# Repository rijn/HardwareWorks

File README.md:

# HardwareWorks
Some hardware module, including schematic, layout and demo code.

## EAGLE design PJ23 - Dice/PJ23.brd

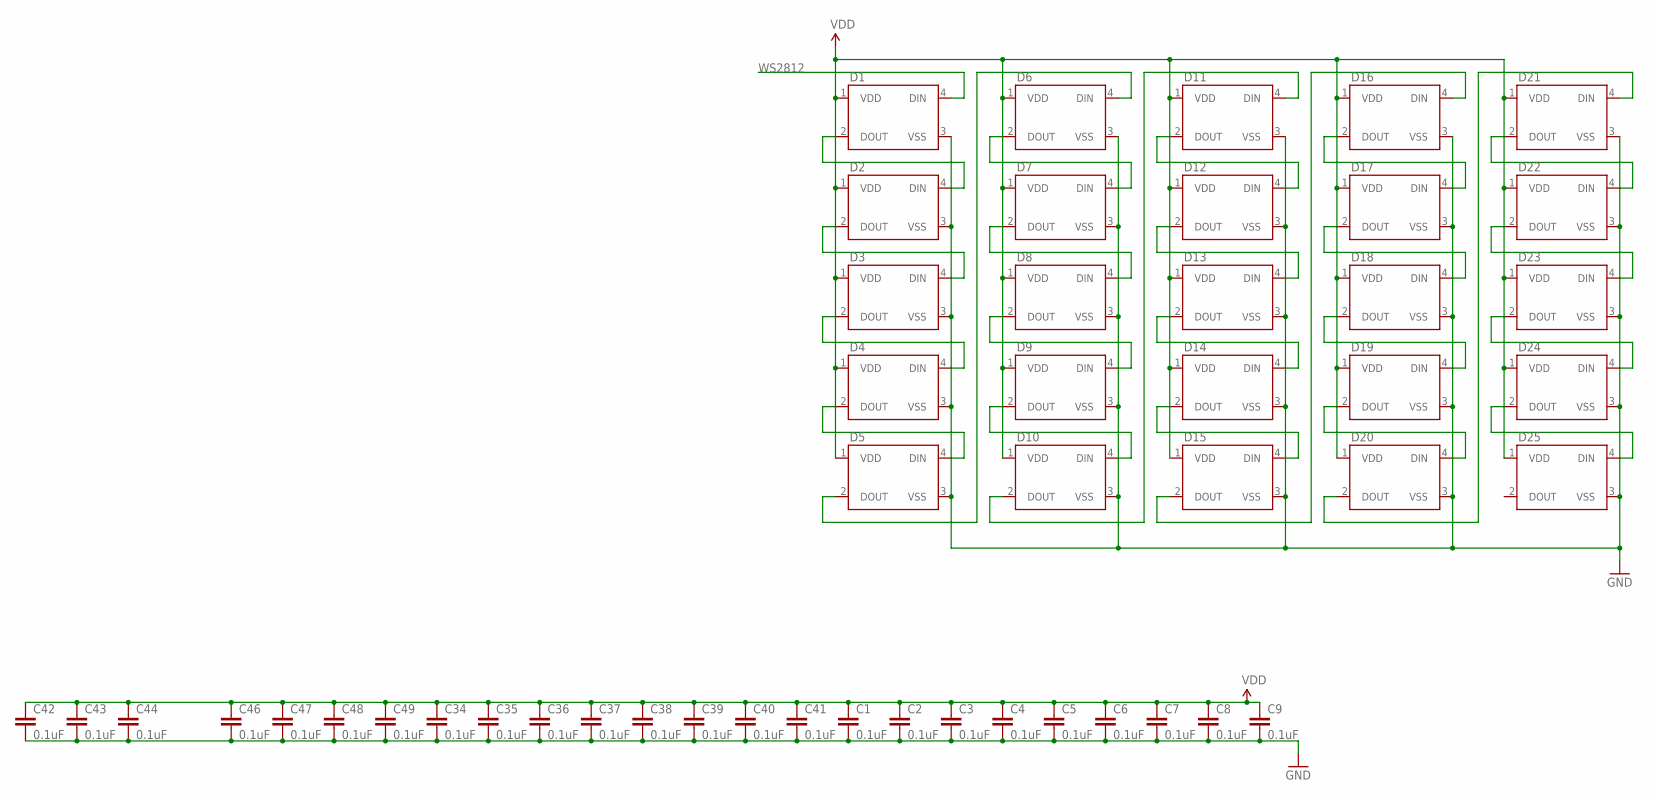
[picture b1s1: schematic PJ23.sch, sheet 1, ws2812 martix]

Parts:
C1, C2, C3, C4, C5, C6, C7, C8, C9, C34, C35, C36, C37, C38, C39, C40, C41, C42, C43, C44, C46, C47, C48, C49: 0.1uF; 0603-CAP
D1, D2, D3, D4, D5, D6, D7, D8, D9, D10, D11, D12, D13, D14, D15, D16, D17, D18, D19, D20, D21, D22, D23, D24, D25: WS2812B

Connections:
GND: C1.2, C2.2, C3.2, C4.2, C5.2, C6.2, C7.2, C8.2, C9.2, C34.2, C35.2, C36.2, C37.2, C38.2, C39.2, C40.2, C41.2, C42.2, C43.2, C44.2, C46.2, C47.2, C48.2, C49.2, D1.3 (VSS), D2.3 (VSS), D3.3 (VSS), D4.3 (VSS), D5.3 (VSS), D6.3 (VSS), D7.3 (VSS), D8.3 (VSS), D9.3 (VSS), D10.3 (VSS), D11.3 (VSS), D12.3 (VSS), D13.3 (VSS), D14.3 (VSS), D15.3 (VSS), D16.3 (VSS), D17.3 (VSS), D18.3 (VSS), D19.3 (VSS), D20.3 (VSS), D21.3 (VSS), D22.3 (VSS), D23.3 (VSS), D24.3 (VSS), D25.3 (VSS); also elsewhere on the board
unnamed: D1.2 (DOUT), D2.4 (DIN)
unnamed: D2.2 (DOUT), D3.4 (DIN)
unnamed: D3.2 (DOUT), D4.4 (DIN)
unnamed: D4.2 (DOUT), D5.4 (DIN)
unnamed: D5.2 (DOUT), D6.4 (DIN)
unnamed: D6.2 (DOUT), D7.4 (DIN)
unnamed: D7.2 (DOUT), D8.4 (DIN)
unnamed: D8.2 (DOUT), D9.4 (DIN)
unnamed: D9.2 (DOUT), D10.4 (DIN)
unnamed: D10.2 (DOUT), D11.4 (DIN)
unnamed: D11.2 (DOUT), D12.4 (DIN)
unnamed: D12.2 (DOUT), D13.4 (DIN)
unnamed: D13.2 (DOUT), D14.4 (DIN)
unnamed: D14.2 (DOUT), D15.4 (DIN)
unnamed: D15.2 (DOUT), D16.4 (DIN)
unnamed: D16.2 (DOUT), D17.4 (DIN)
unnamed: D17.2 (DOUT), D18.4 (DIN)
unnamed: D18.2 (DOUT), D19.4 (DIN)
unnamed: D19.2 (DOUT), D20.4 (DIN)
unnamed: D20.2 (DOUT), D21.4 (DIN)
unnamed: D21.2 (DOUT), D22.4 (DIN)
unnamed: D22.2 (DOUT), D23.4 (DIN)
unnamed: D23.2 (DOUT), D24.4 (DIN)
unnamed: D24.2 (DOUT), D25.4 (DIN)
VDD: C1.1, C2.1, C3.1, C4.1, C5.1, C6.1, C7.1, C8.1, C9.1, C34.1, C35.1, C36.1, C37.1, C38.1, C39.1, C40.1, C41.1, C42.1, C43.1, C44.1, C46.1, C47.1, C48.1, C49.1, D1.1 (VDD), D2.1 (VDD), D3.1 (VDD), D4.1 (VDD), D5.1 (VDD), D6.1 (VDD), D7.1 (VDD), D8.1 (VDD), D9.1 (VDD), D10.1 (VDD), D11.1 (VDD), D12.1 (VDD), D13.1 (VDD), D14.1 (VDD), D15.1 (VDD), D16.1 (VDD), D17.1 (VDD), D18.1 (VDD), D19.1 (VDD), D20.1 (VDD), D21.1 (VDD), D22.1 (VDD), D23.1 (VDD), D24.1 (VDD), D25.1 (VDD); also elsewhere on the board
WS2812: D1.4 (DIN); also elsewhere on the board

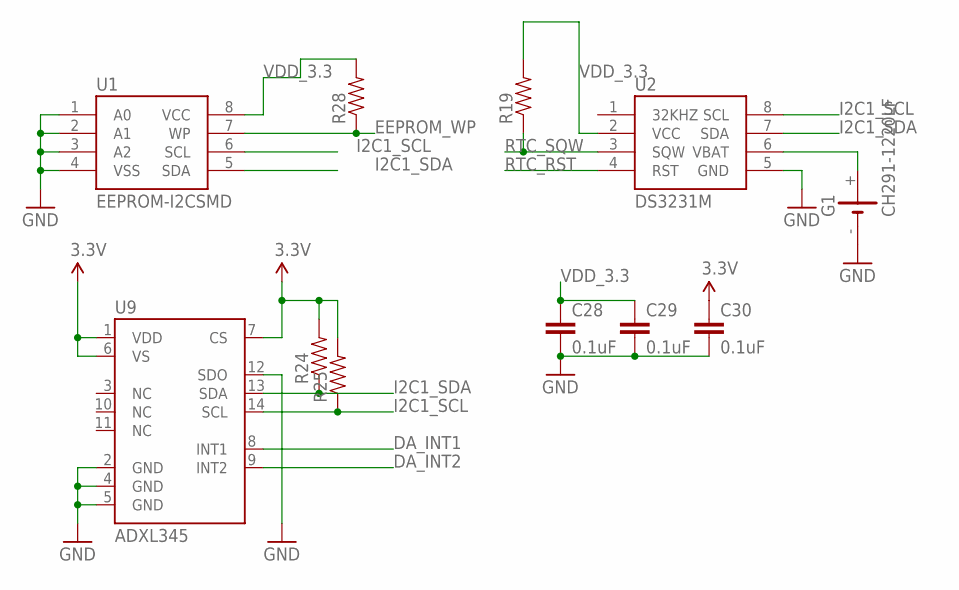
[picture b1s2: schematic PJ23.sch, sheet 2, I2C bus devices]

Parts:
C28, C29, C30: 0.1uF; 0603-CAP
G1: CH291-1220LF
R19, R24, R25, R28: RESISTOR0603; 0603-RES
U1: EEPROM-I2CSMD; SO08
U2: DS3231M; SOIC8
U9: ADXL345; LGA14

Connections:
3.3V: C30.1, R24.2, R25.2, U9.1 (VDD), U9.6 (VS), U9.7 (CS); also elsewhere on the board
DA_INT1: U9.8 (INT1); also elsewhere on the board
DA_INT2: U9.9 (INT2); also elsewhere on the board
EEPROM_WP: R28.1, U1.7 (WP); also elsewhere on the board
GND: C28.2, C29.2, C30.2, G1.-, U1.1 (A0), U1.2 (A1), U1.3 (A2), U1.4 (VSS), U2.5 (GND), U9.2 (GND), U9.4 (GND), U9.5 (GND), U9.12 (SDO); also elsewhere on the board
I2C1_SCL: R25.1, U1.6 (SCL), U2.8 (SCL), U9.14 (SCL); also elsewhere on the board
I2C1_SDA: R24.1, U1.5 (SDA), U2.7 (SDA), U9.13 (SDA); also elsewhere on the board
unnamed: G1.+, U2.6 (VBAT)
RTC_RST: U2.4 (RST)
RTC_SQW: R19.1, U2.3 (SQW)
VDD_3.3: C28.1, C29.1, R19.2, R28.2, U1.8 (VCC), U2.2 (VCC); also elsewhere on the board

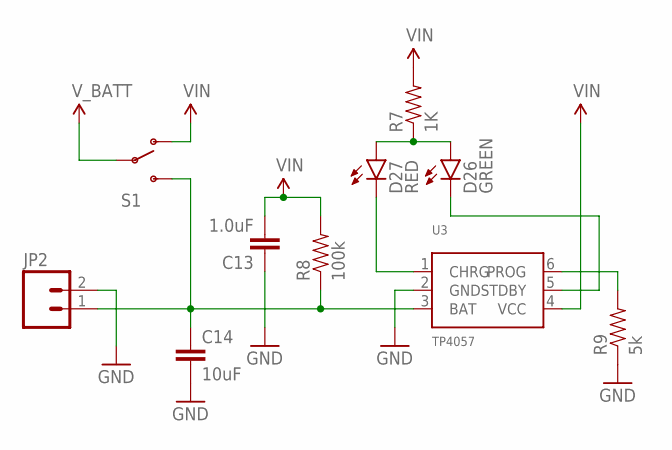
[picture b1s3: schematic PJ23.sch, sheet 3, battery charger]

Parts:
C13: 1.0uF; 0805-CAP
C14: 10uF; 1206
D26: GREEN; LED-0603
D27: RED; LED-0603
JP2: M02LOCK; 1X02_LOCK
R7: 1K; 0603-RES
R8: 100k; 0603-RES
R9: 5k; 0805
S1: SWITCH-SPDT-SMD-A; SWITCH-SPST-SMD-A
U3: TP4057; SOT23-6

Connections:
GND: C13.1, C14.2, JP2.2, R9.1, U3.2 (GND); also elsewhere on the board
unnamed: D27.C, U3.1 (CHRG)
unnamed: D26.C, U3.5 (STDBY)
unnamed: D26.A, D27.A, R7.1
unnamed: C14.1, JP2.1, R8.1, S1.3 (S), U3.3 (BAT)
unnamed: R9.2, U3.6 (PROG)
VIN: C13.2, R7.2, R8.2, S1.1 (O), U3.4 (VCC); also elsewhere on the board
V_BATT: S1.2; also elsewhere on the board

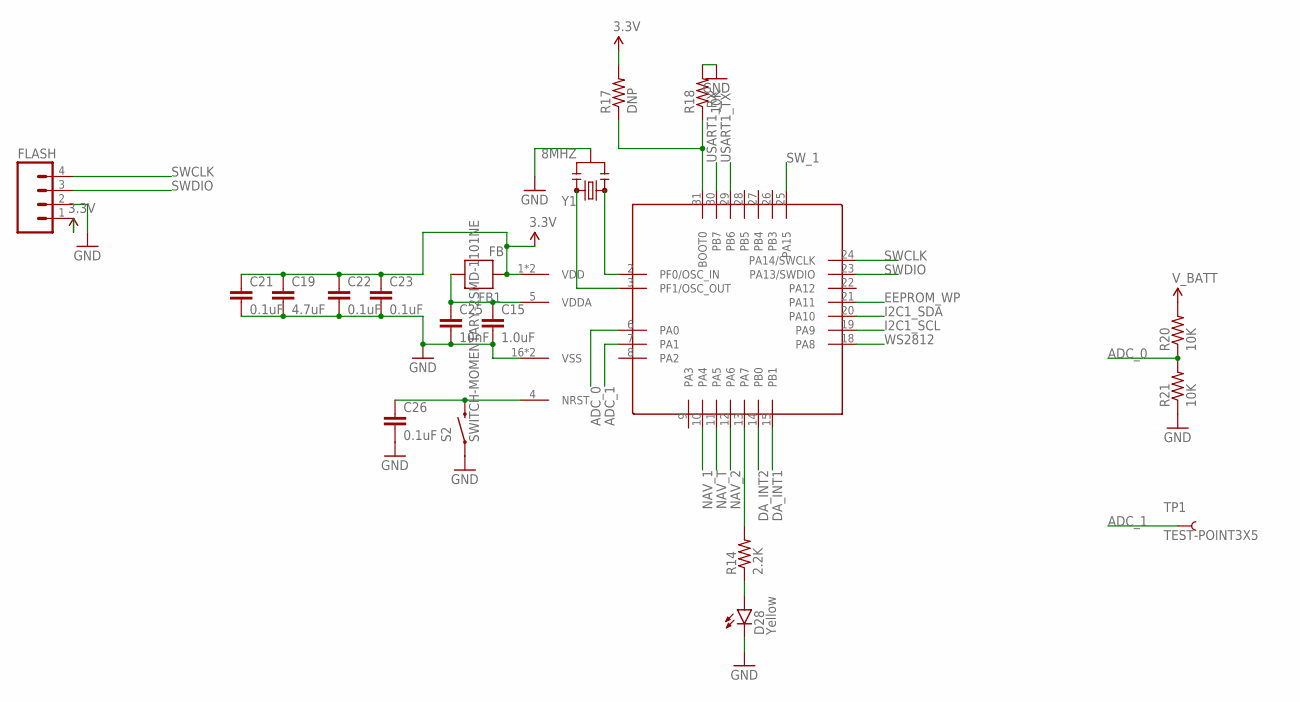
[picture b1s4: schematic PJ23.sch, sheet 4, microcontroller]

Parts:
C15: 1.0uF; 0603-CAP
C19: 4.7uF; 0603-CAP
C21, C22, C23, C26: 0.1uF; 0402-CAP
C25: 10nF; 0402-CAP
D28: Yellow; LED-0603
FB1: FB; 0603
FLASH: M04SMD; 1X04-SMD
R14: 2.2K; 0402-RES
R17: DNP; 0402-RES
R18, R20, R21: 10K; 0402-RES
S2: SWITCH-MOMENTARY-2SMD-1101NE; TACTILE-SWITCH-1101NE
TP1: TEST-POINT3X5; PAD.03X.05
U7: STM32F030K6P6; LQFP32-0.8
Y1: 8MHZ; RESONATOR-SMD

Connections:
3.3V: C19.1, C21.1, C22.1, C23.1, FB1.2, FLASH.1, R17.2, U7.1 (VDD), U7.17 (VDD); also elsewhere on the board
ADC_0: R20.1, R21.2, U7.6 (PA0)
ADC_1: TP1.P$1, U7.7 (PA1)
DA_INT1: U7.15 (PB1); also elsewhere on the board
DA_INT2: U7.14 (PB0); also elsewhere on the board
EEPROM_WP: U7.21 (PA11); also elsewhere on the board
GND: C15.2, C19.2, C21.2, C22.2, C23.2, C25.2, C26.2, D28.C, FLASH.2, R18.2, R21.1, S2.1, U7.16 (VSS), U7.32 (VSS), Y1.2; also elsewhere on the board
I2C1_SCL: U7.19 (PA9); also elsewhere on the board
I2C1_SDA: U7.20 (PA10); also elsewhere on the board
unnamed: C15.1, C25.1, FB1.1, U7.5 (VDDA)
unnamed: R17.1, R18.1, U7.31 (BOOT0)
unnamed: D28.A, R14.1
unnamed: C26.1, S2.2, U7.4 (NRST)
unnamed: R14.2, U7.13 (PA7)
NAV_1: U7.10 (PA4); also elsewhere on the board
NAV_2: U7.12 (PA6); also elsewhere on the board
NAV_T: U7.11 (PA5); also elsewhere on the board
PF0: U7.2 (PF0/OSC_IN), Y1.1
PF1: U7.3 (PF1/OSC_OUT), Y1.3
SWCLK: FLASH.4, U7.24 (PA14/SWCLK)
SWDIO: FLASH.3, U7.23 (PA13/SWDIO)
SW_1: U7.25 (PA15); also elsewhere on the board
USART1_RX: U7.30 (PB7); also elsewhere on the board
USART1_TX: U7.29 (PB6); also elsewhere on the board
V_BATT: R20.2; also elsewhere on the board
WS2812: U7.18 (PA8); also elsewhere on the board

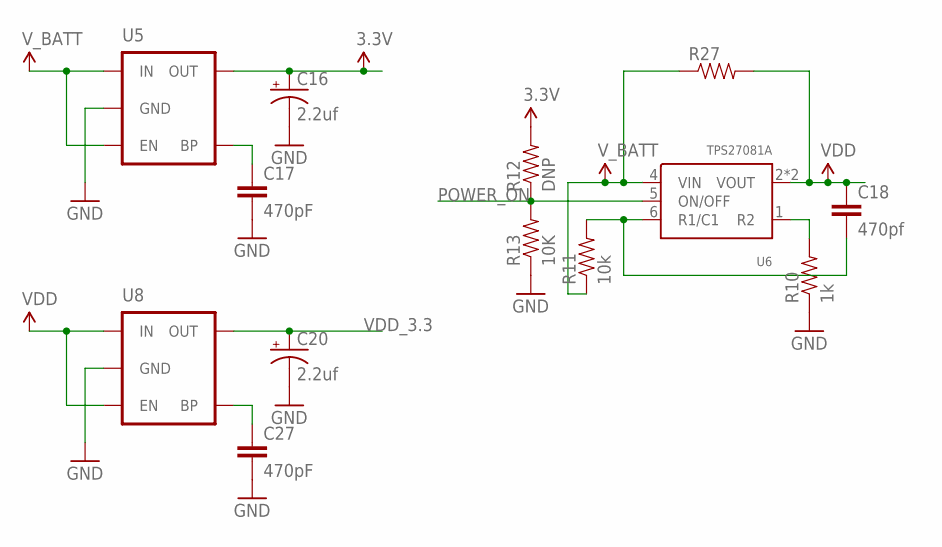
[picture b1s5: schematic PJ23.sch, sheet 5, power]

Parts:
C16, C20: 2.2uf; EIA3216
C17, C27: 470pF; 0805
C18: 470pf; 1206
R10: 1k; 0805
R11: 10k; 0805
R12: DNP; 0603-RES
R13: 10K; 0603-RES
R27: RESISTOR0805-RES; 0805
U5, U8: MIC52053.3V; SOT23-5
U6: TPS27081A; DDC(R-PDSO-G6)

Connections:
3.3V: C16.A (+), R12.2, U5.5 (OUT); also elsewhere on the board
GND: C16.C (-), C17.2, C20.C (-), C27.2, R10.1, R13.1, U5.2 (GND), U8.2 (GND); also elsewhere on the board
unnamed: R10.2, U6.1 (R2)
unnamed: C18.2, R11.2, U6.6 (R1/C1)
unnamed: C17.1, U5.4 (BP)
unnamed: C27.1, U8.4 (BP)
POWER_ON: R12.1, R13.2, U6.5 (ON/OFF)
VDD: C18.1, R27.2, U6.2 (VOUT), U6.3 (VOUT), U8.1 (IN), U8.3 (EN); also elsewhere on the board
VDD_3.3: C20.A (+), U8.5 (OUT); also elsewhere on the board
V_BATT: R11.1, R27.1, U5.1 (IN), U5.3 (EN), U6.4 (VIN); also elsewhere on the board

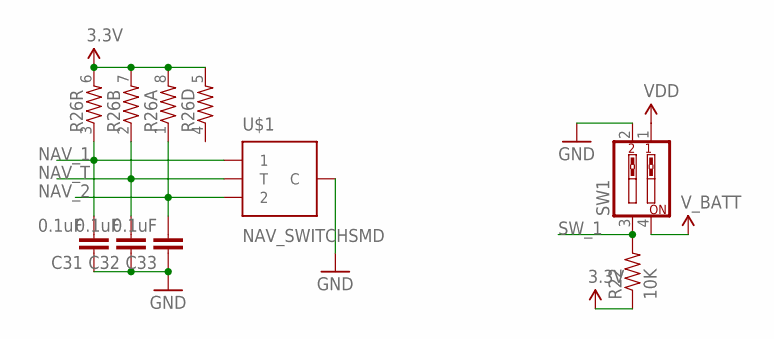
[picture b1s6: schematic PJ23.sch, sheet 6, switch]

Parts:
C31, C32, C33: 0.1uF; 0603-CAP
R22: 10K; 0603-RES
R26: RESISTOR-ARRAY0603-ARV; 0603-ARV
SW1: SW_DIP-2-SMT-HALFSIZE; DIPSWITCH-02-50MIL
U$1: NAV_SWITCHSMD; NAV_SWITCH

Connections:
3.3V: R22.1, R26.5 (2), R26.6 (2), R26.7 (2), R26.8 (2); also elsewhere on the board
GND: C31.1, C32.1, C33.1, SW1.2, U$1.C; also elsewhere on the board
NAV_1: C31.2, R26.3 (1), U$1.1; also elsewhere on the board
NAV_2: C33.2, R26.1, U$1.2; also elsewhere on the board
NAV_T: C32.2, R26.2 (1), U$1.T; also elsewhere on the board
SW_1: R22.2, SW1.3; also elsewhere on the board
VDD: SW1.1; also elsewhere on the board
V_BATT: SW1.4; also elsewhere on the board

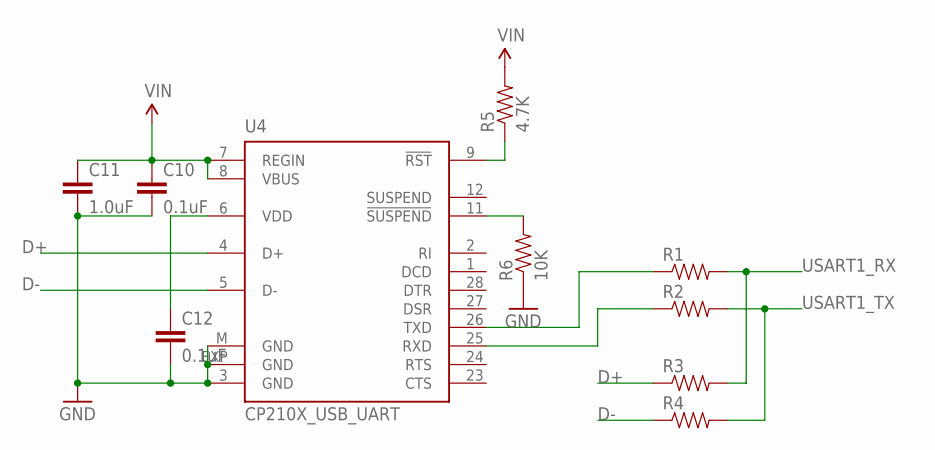
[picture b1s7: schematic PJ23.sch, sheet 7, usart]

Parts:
C10, C12: 0.1uF; 0603-CAP
C11: 1.0uF; 0805-CAP
R1, R2, R3, R4: RESISTOR0603; 0603-RES
R5: 4.7K; 0603-RES
R6: 10K; 0603-RES
U4: CP210X_USB_UART; MLP28

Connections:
D+: R3.1, U4.4 (D+); also elsewhere on the board
D-: R4.1, U4.5 (D-); also elsewhere on the board
GND: C10.2, C11.2, C12.2, R6.1, U4.3 (GND), U4.EXP (GND), U4.M (GND); also elsewhere on the board
unnamed: C12.1, U4.6 (VDD)
unnamed: R5.1, U4.9 (!RST)
unnamed: R6.2, U4.11 (!SUSPEND)
unnamed: R1.1, U4.26 (TXD)
unnamed: R2.1, U4.25 (RXD)
USART1_RX: R1.2, R3.2; also elsewhere on the board
USART1_TX: R2.2, R4.2; also elsewhere on the board
VIN: C10.1, C11.1, R5.2, U4.7 (REGIN), U4.8 (VBUS); also elsewhere on the board

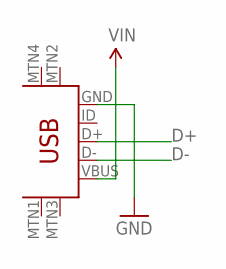
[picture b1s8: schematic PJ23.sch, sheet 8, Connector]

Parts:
JP1: USB-MINIB-5PIN; USB-MINIB

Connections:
D+: JP1.D+; also elsewhere on the board
D-: JP1.D-; also elsewhere on the board
GND: JP1.GND; also elsewhere on the board
VIN: JP1.VBUS; also elsewhere on the board

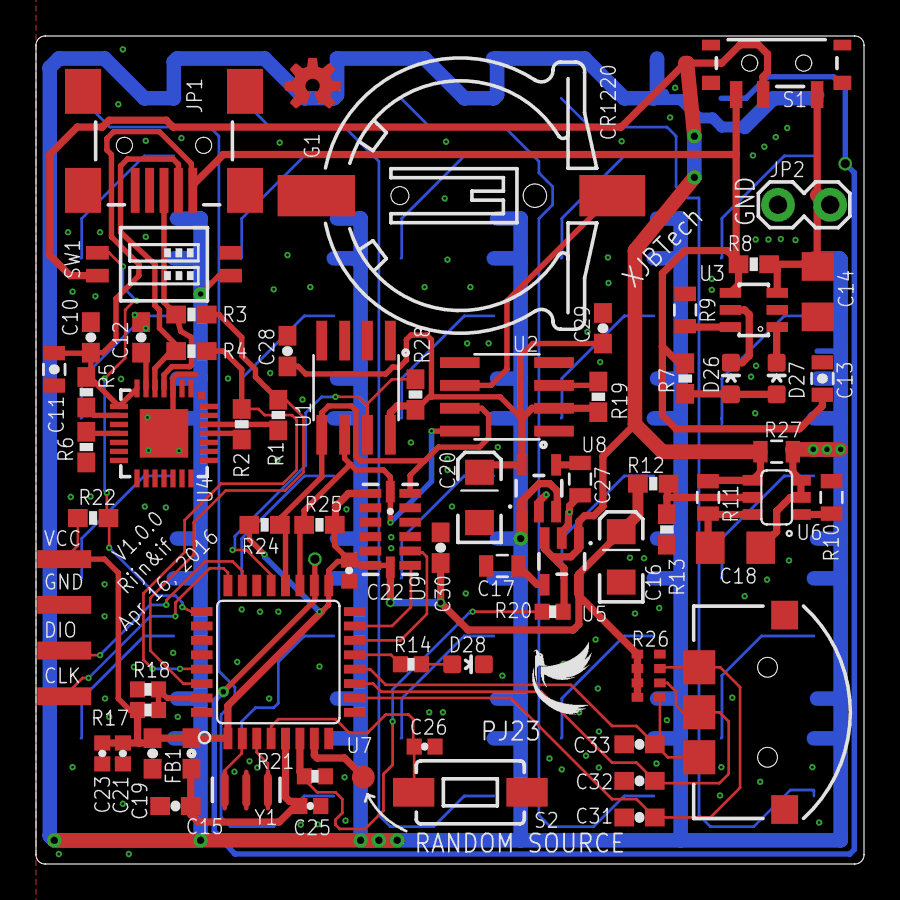
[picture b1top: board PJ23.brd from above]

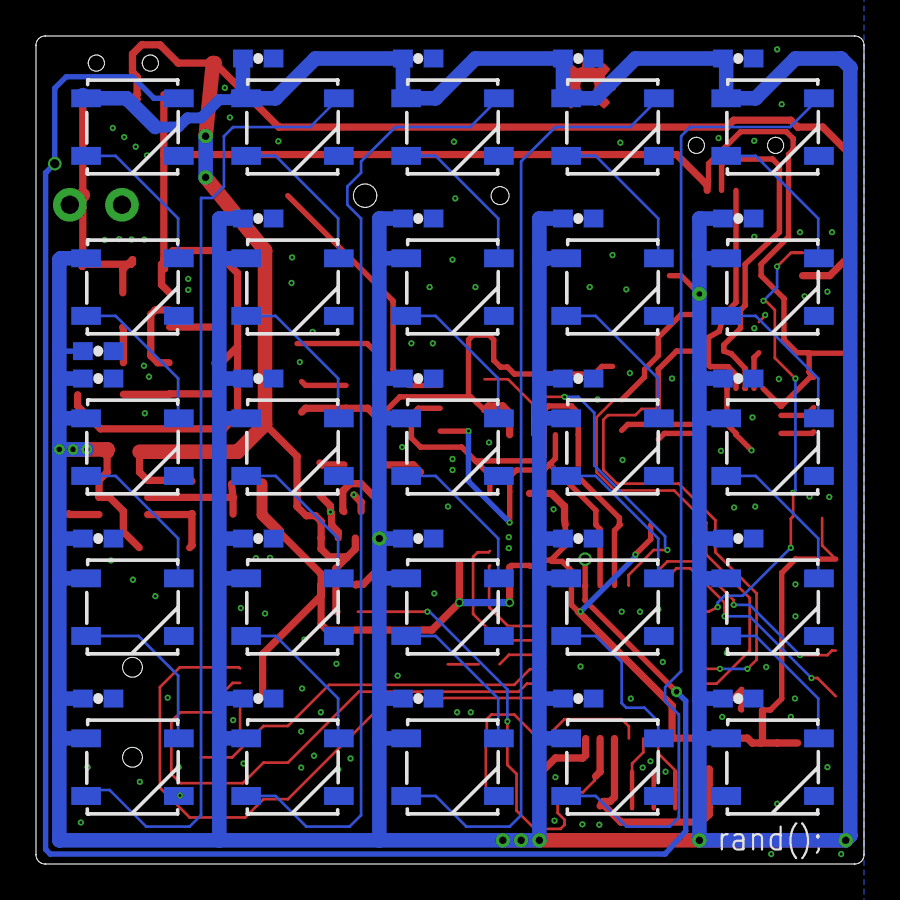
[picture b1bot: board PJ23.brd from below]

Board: 2 copper layers, 46.0 x 46.0 mm, 122 parts (49 on the bottom side), 72 nets.

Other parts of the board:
U$2: LOGO
U$3: OSHW-LOGO-S_COPPER

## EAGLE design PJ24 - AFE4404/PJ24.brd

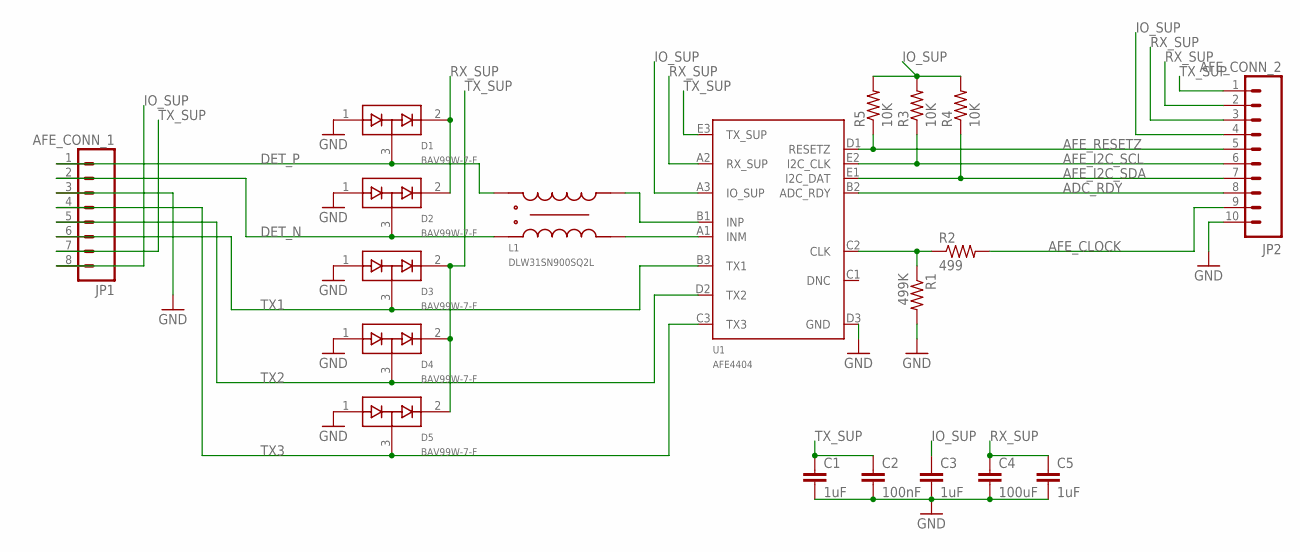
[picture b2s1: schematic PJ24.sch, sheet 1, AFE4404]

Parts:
C1, C3, C5: 1uF; 0402-S
C2: 100nF; 0402-S
C4: 100uF; 0402-S
D1, D2, D3, D4, D5: BAV99W-7-F; SOT323
JP1: AFE_CONN_1; BM08B-SRSS-TB
JP2: AFE_CONN_2; 1X10_SMD_MALE
L1: DLW31SN900SQ2L
R1: 499K; 0402-S
R2: 499; 0402-S
R3, R4, R5: 10K; 0402-S
U1: AFE4404; DSBGA-3X5

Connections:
ADC_RDY: JP2.8, U1.B2 (ADC_RDY); also elsewhere on the board
AFE_CLOCK: JP2.9, R2.2; also elsewhere on the board
AFE_I2C_SCL: JP2.6, R3.1, U1.E2 (I2C_CLK); also elsewhere on the board
AFE_I2C_SDA: JP2.7, R4.1, U1.E1 (I2C_DAT); also elsewhere on the board
AFE_RESETZ: JP2.5, R5.1, U1.D1 (RESETZ); also elsewhere on the board
DET_N: D2.3 (COM), JP1.2, L1.4; also elsewhere on the board
DET_P: D1.3 (COM), JP1.1, L1.1; also elsewhere on the board
GND: C1.2, C2.2, C3.2, C4.2, C5.2, D1.1 (A1), D2.1 (A1), D3.1 (A1), D4.1 (A1), D5.1 (A1), JP1.3, JP2.10, R1.2, U1.D3 (GND); also elsewhere on the board
IO_SUP: C3.1, JP1.8, JP2.4, R3.2, R4.2, R5.2, U1.A3 (IO_SUP); also elsewhere on the board
unnamed: L1.2, U1.B1 (INP)
unnamed: L1.3, U1.A1 (INM)
unnamed: R1.1, R2.1, U1.C2 (CLK)
RX_SUP: C4.1, C5.1, D1.2 (C2), D2.2 (C2), JP2.2, JP2.3, U1.A2 (RX_SUP); also elsewhere on the board
TX1: D3.3 (COM), JP1.6, U1.B3 (TX1); also elsewhere on the board
TX2: D4.3 (COM), JP1.5, U1.D2 (TX2); also elsewhere on the board
TX3: D5.3 (COM), JP1.4, U1.C3 (TX3); also elsewhere on the board
TX_SUP: C1.1, C2.1, D3.2 (C2), D4.2 (C2), D5.2 (C2), JP1.7, JP2.1, U1.E3 (TX_SUP); also elsewhere on the board

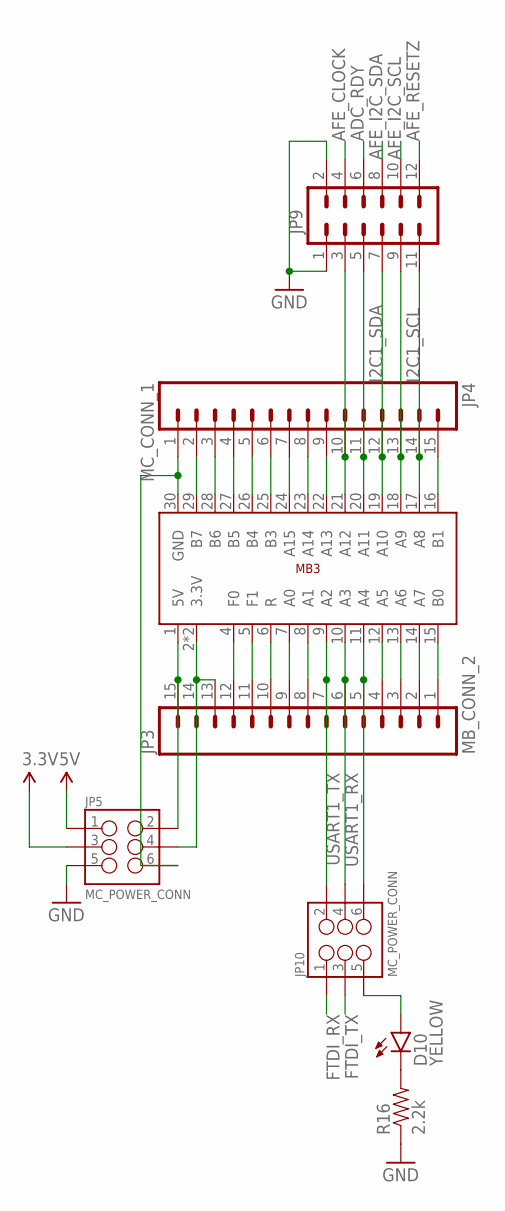
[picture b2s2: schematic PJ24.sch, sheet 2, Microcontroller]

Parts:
D10: YELLOW; LED-1206
JP3: MB_CONN_2; 1X15_LOCK
JP4: MC_CONN_1; 1X15_LOCK
JP5, JP10: MC_POWER_CONN; 2X3_SMT_POSTS
JP9: M06X2FEMALE-SMT; 2X6_SMD
R16: 2.2k; 0603-RES
U2: MB3

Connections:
3.3V: JP5.3; also elsewhere on the board
5V: JP5.1; also elsewhere on the board
ADC_RDY: JP9.6; also elsewhere on the board
AFE_CLOCK: JP9.4; also elsewhere on the board
AFE_I2C_SCL: JP9.10; also elsewhere on the board
AFE_I2C_SDA: JP9.8; also elsewhere on the board
AFE_RESETZ: JP9.12; also elsewhere on the board
FTDI_RX: JP10.1; also elsewhere on the board
FTDI_TX: JP10.3; also elsewhere on the board
GND: JP5.5, JP9.1, JP9.2, R16.1; also elsewhere on the board
I2C1_SCL: JP4.13, JP9.9, U2.18 (A9)
I2C1_SDA: JP4.12, JP9.7, U2.19 (A10)
unnamed: JP3.15, JP5.2, U2.1 (5V)
unnamed: JP3.13, JP3.14, JP5.4, U2.2 (3.3V), U2.3 (3.3V)
unnamed: JP3.12, U2.4 (F0)
unnamed: JP3.11, U2.5 (F1)
unnamed: JP3.10, U2.6 (R)
unnamed: JP3.9, U2.7 (A0)
unnamed: JP3.8, U2.8 (A1)
unnamed: D10.C, R16.2
unnamed: D10.A, JP10.5
unnamed: JP3.5, JP10.6, U2.11 (A4)
unnamed: JP3.4, U2.12 (A5)
unnamed: JP3.3, U2.13 (A6)
unnamed: JP3.2, U2.14 (A7)
unnamed: JP3.1, U2.15 (B0)
unnamed: JP4.1, JP5.6, U2.30 (GND)
unnamed: JP4.2, U2.29 (B7)
unnamed: JP4.3, U2.28 (B6)
unnamed: JP4.4, U2.27 (B5)
unnamed: JP4.5, U2.26 (B4)
unnamed: JP4.6, U2.25 (B3)
unnamed: JP4.7, U2.24 (A15)
unnamed: JP4.8, U2.23 (A14)
unnamed: JP4.9, U2.22 (A13)
unnamed: JP4.10, JP9.3, U2.21 (A12)
unnamed: JP4.11, JP9.5, U2.20 (A11)
unnamed: JP4.14, JP9.11, U2.17 (A8)
unnamed: JP4.15, U2.16 (B1)
USART1_RX: JP3.6, JP10.4, U2.10 (A3)
USART1_TX: JP3.7, JP10.2, U2.9 (A2)

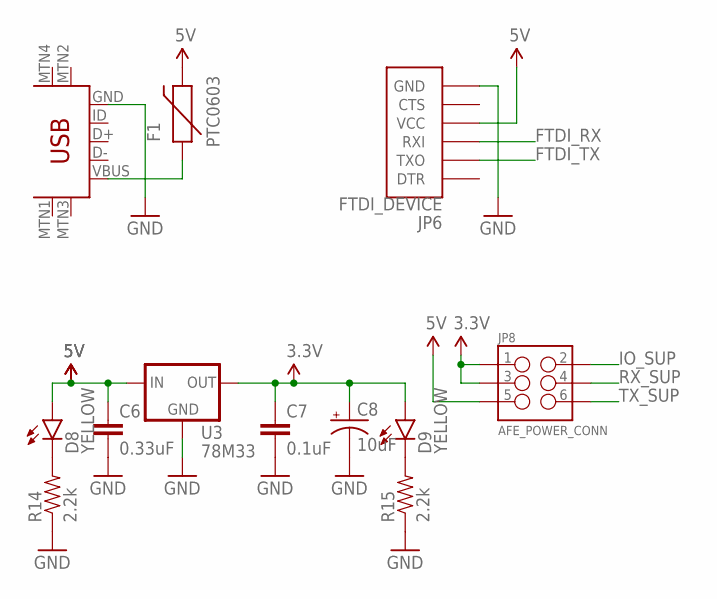
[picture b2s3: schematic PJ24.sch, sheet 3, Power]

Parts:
C6: 0.33uF; 0805-CAP
C7: 0.1uF; 0805-CAP
C8: 10uF; EIA3216
D8, D9: YELLOW; LED-1206
F1: PTC0603; 0603
JP6: FTDI_DEVICE; FTDI_DEVICE_SIDE
JP8: AFE_POWER_CONN; 2X3_SMT_POSTS
R14, R15: 2.2k; 0603-RES
U3: 78M33; TO-252
U$1: USB-MINIB-5PIN; USB-MINIB

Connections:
3.3V: C7.1, C8.A (+), D9.A, JP8.1, JP8.3, U3.2 (OUT); also elsewhere on the board
5V: C6.1, D8.A, F1.2, JP6.P$4 (VCC), JP8.5, U3.1 (IN); also elsewhere on the board
FTDI_RX: JP6.P$3 (RXI); also elsewhere on the board
FTDI_TX: JP6.P$2 (TXO); also elsewhere on the board
GND: C6.2, C7.2, C8.C (-), JP6.P$6 (GND), R14.1, R15.1, U3.3 (GND), U$1.GND; also elsewhere on the board
IO_SUP: JP8.2; also elsewhere on the board
unnamed: D8.C, R14.2
unnamed: D9.C, R15.2
unnamed: F1.1, U$1.VBUS
RX_SUP: JP8.4; also elsewhere on the board
TX_SUP: JP8.6; also elsewhere on the board

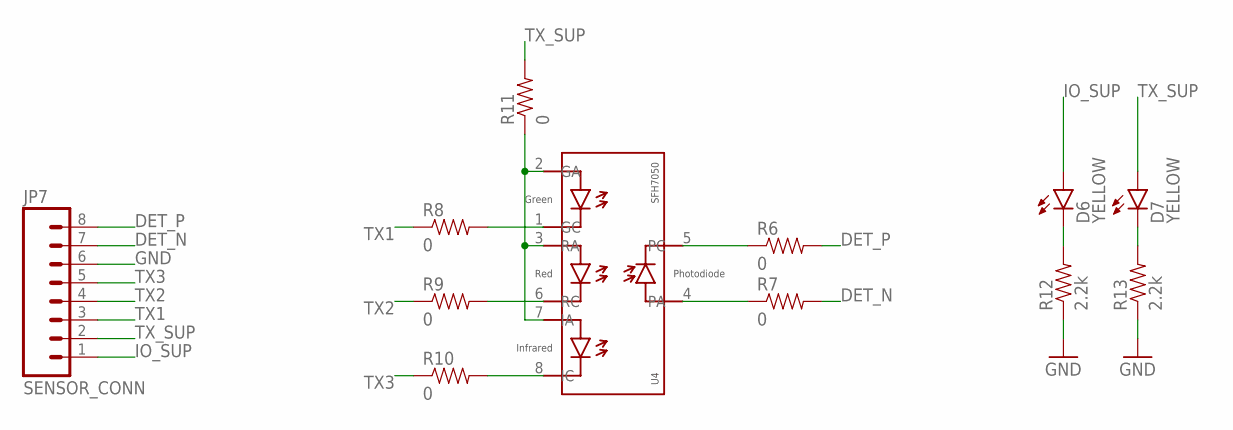
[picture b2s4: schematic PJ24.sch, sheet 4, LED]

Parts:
D6, D7: YELLOW; LED-1206
JP7: SENSOR_CONN; BM08B-SRSS-TB
R6, R7, R8, R9, R10, R11: 0; 0402-S
R12, R13: 2.2k; 0603-RES
U4: SFH7050

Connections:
DET_N: JP7.7, R7.2; also elsewhere on the board
DET_P: JP7.8, R6.2; also elsewhere on the board
GND: JP7.6, R12.1, R13.1; also elsewhere on the board
IO_SUP: D6.A, JP7.1; also elsewhere on the board
unnamed: R9.2, U4.6 (RC)
unnamed: R11.1, U4.2 (GA), U4.3 (RA), U4.7 (IA)
unnamed: R10.2, U4.8 (IC)
unnamed: D6.C, R12.2
unnamed: R8.2, U4.1 (GC)
unnamed: D7.C, R13.2
unnamed: R7.1, U4.4 (PA)
unnamed: R6.1, U4.5 (PC)
TX1: JP7.3, R8.1; also elsewhere on the board
TX2: JP7.4, R9.1; also elsewhere on the board
TX3: JP7.5, R10.1; also elsewhere on the board
TX_SUP: D7.A, JP7.2, R11.2; also elsewhere on the board

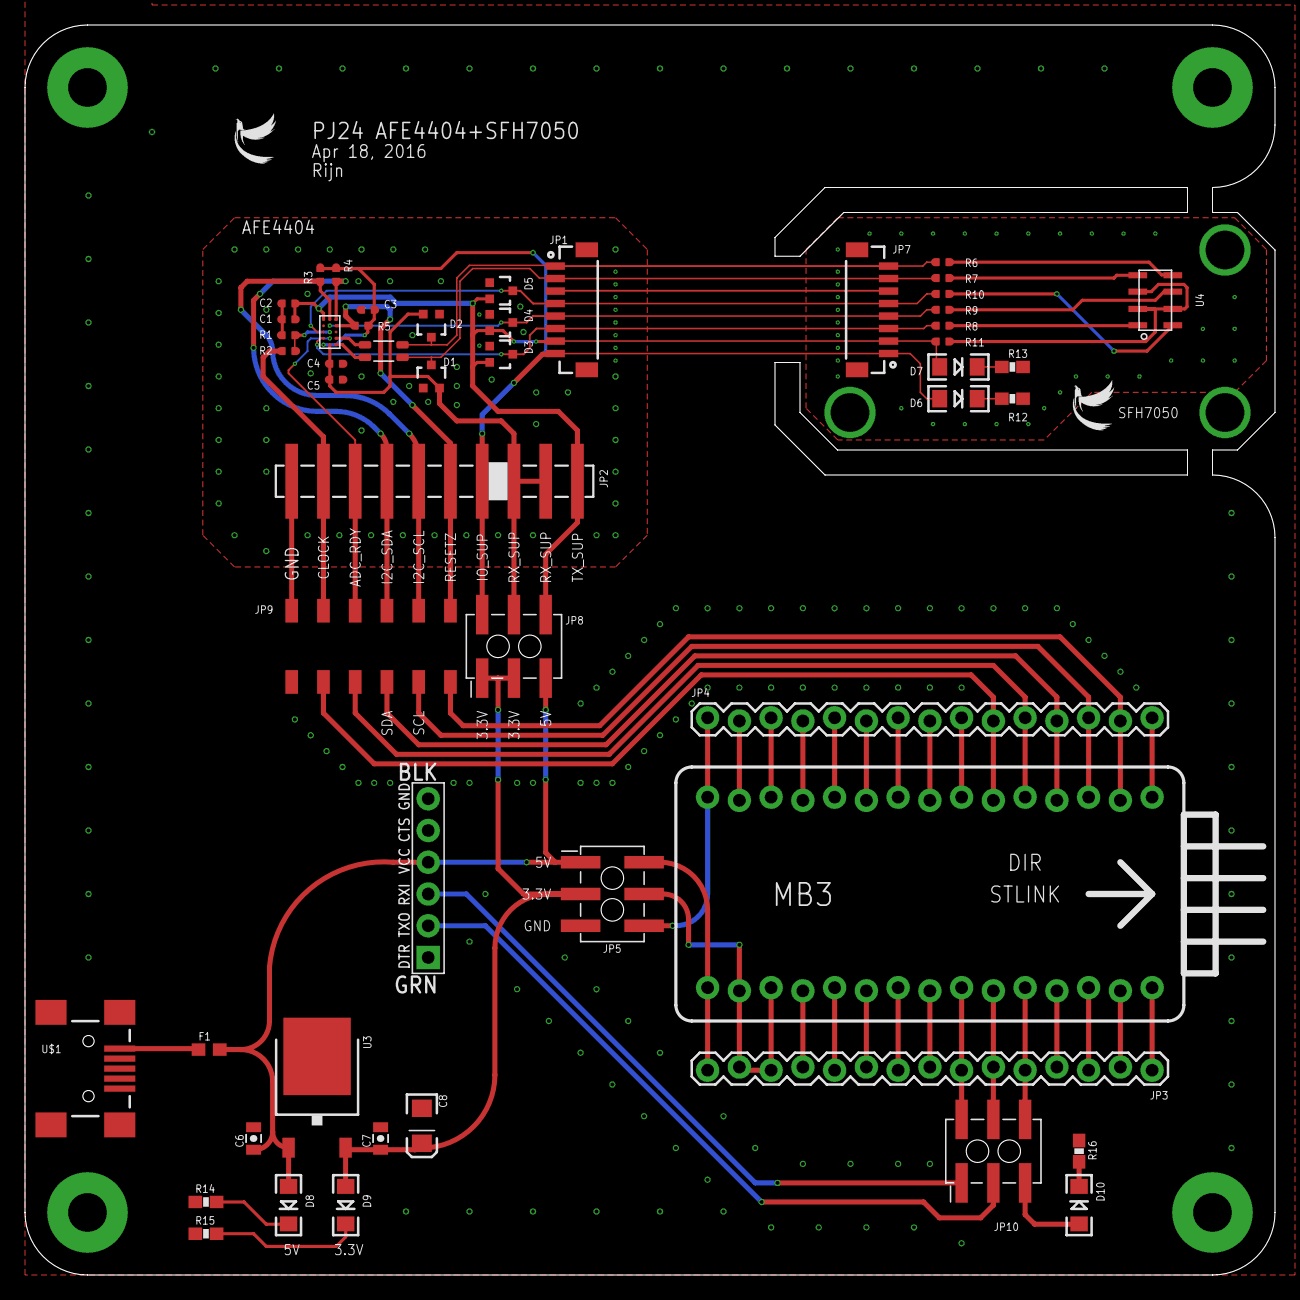
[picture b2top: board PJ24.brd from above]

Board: 2 copper layers, 100.0 x 100.0 mm, 53 parts (0 on the bottom side), 63 nets.

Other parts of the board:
U$2, U$3: LOGO

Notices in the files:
parts and their libraries:
SparkFun-Capacitors: Licensing: Creative Commons ShareAlike 4.0 International - https://creativecommons.org/licenses/by-sa/4.0
